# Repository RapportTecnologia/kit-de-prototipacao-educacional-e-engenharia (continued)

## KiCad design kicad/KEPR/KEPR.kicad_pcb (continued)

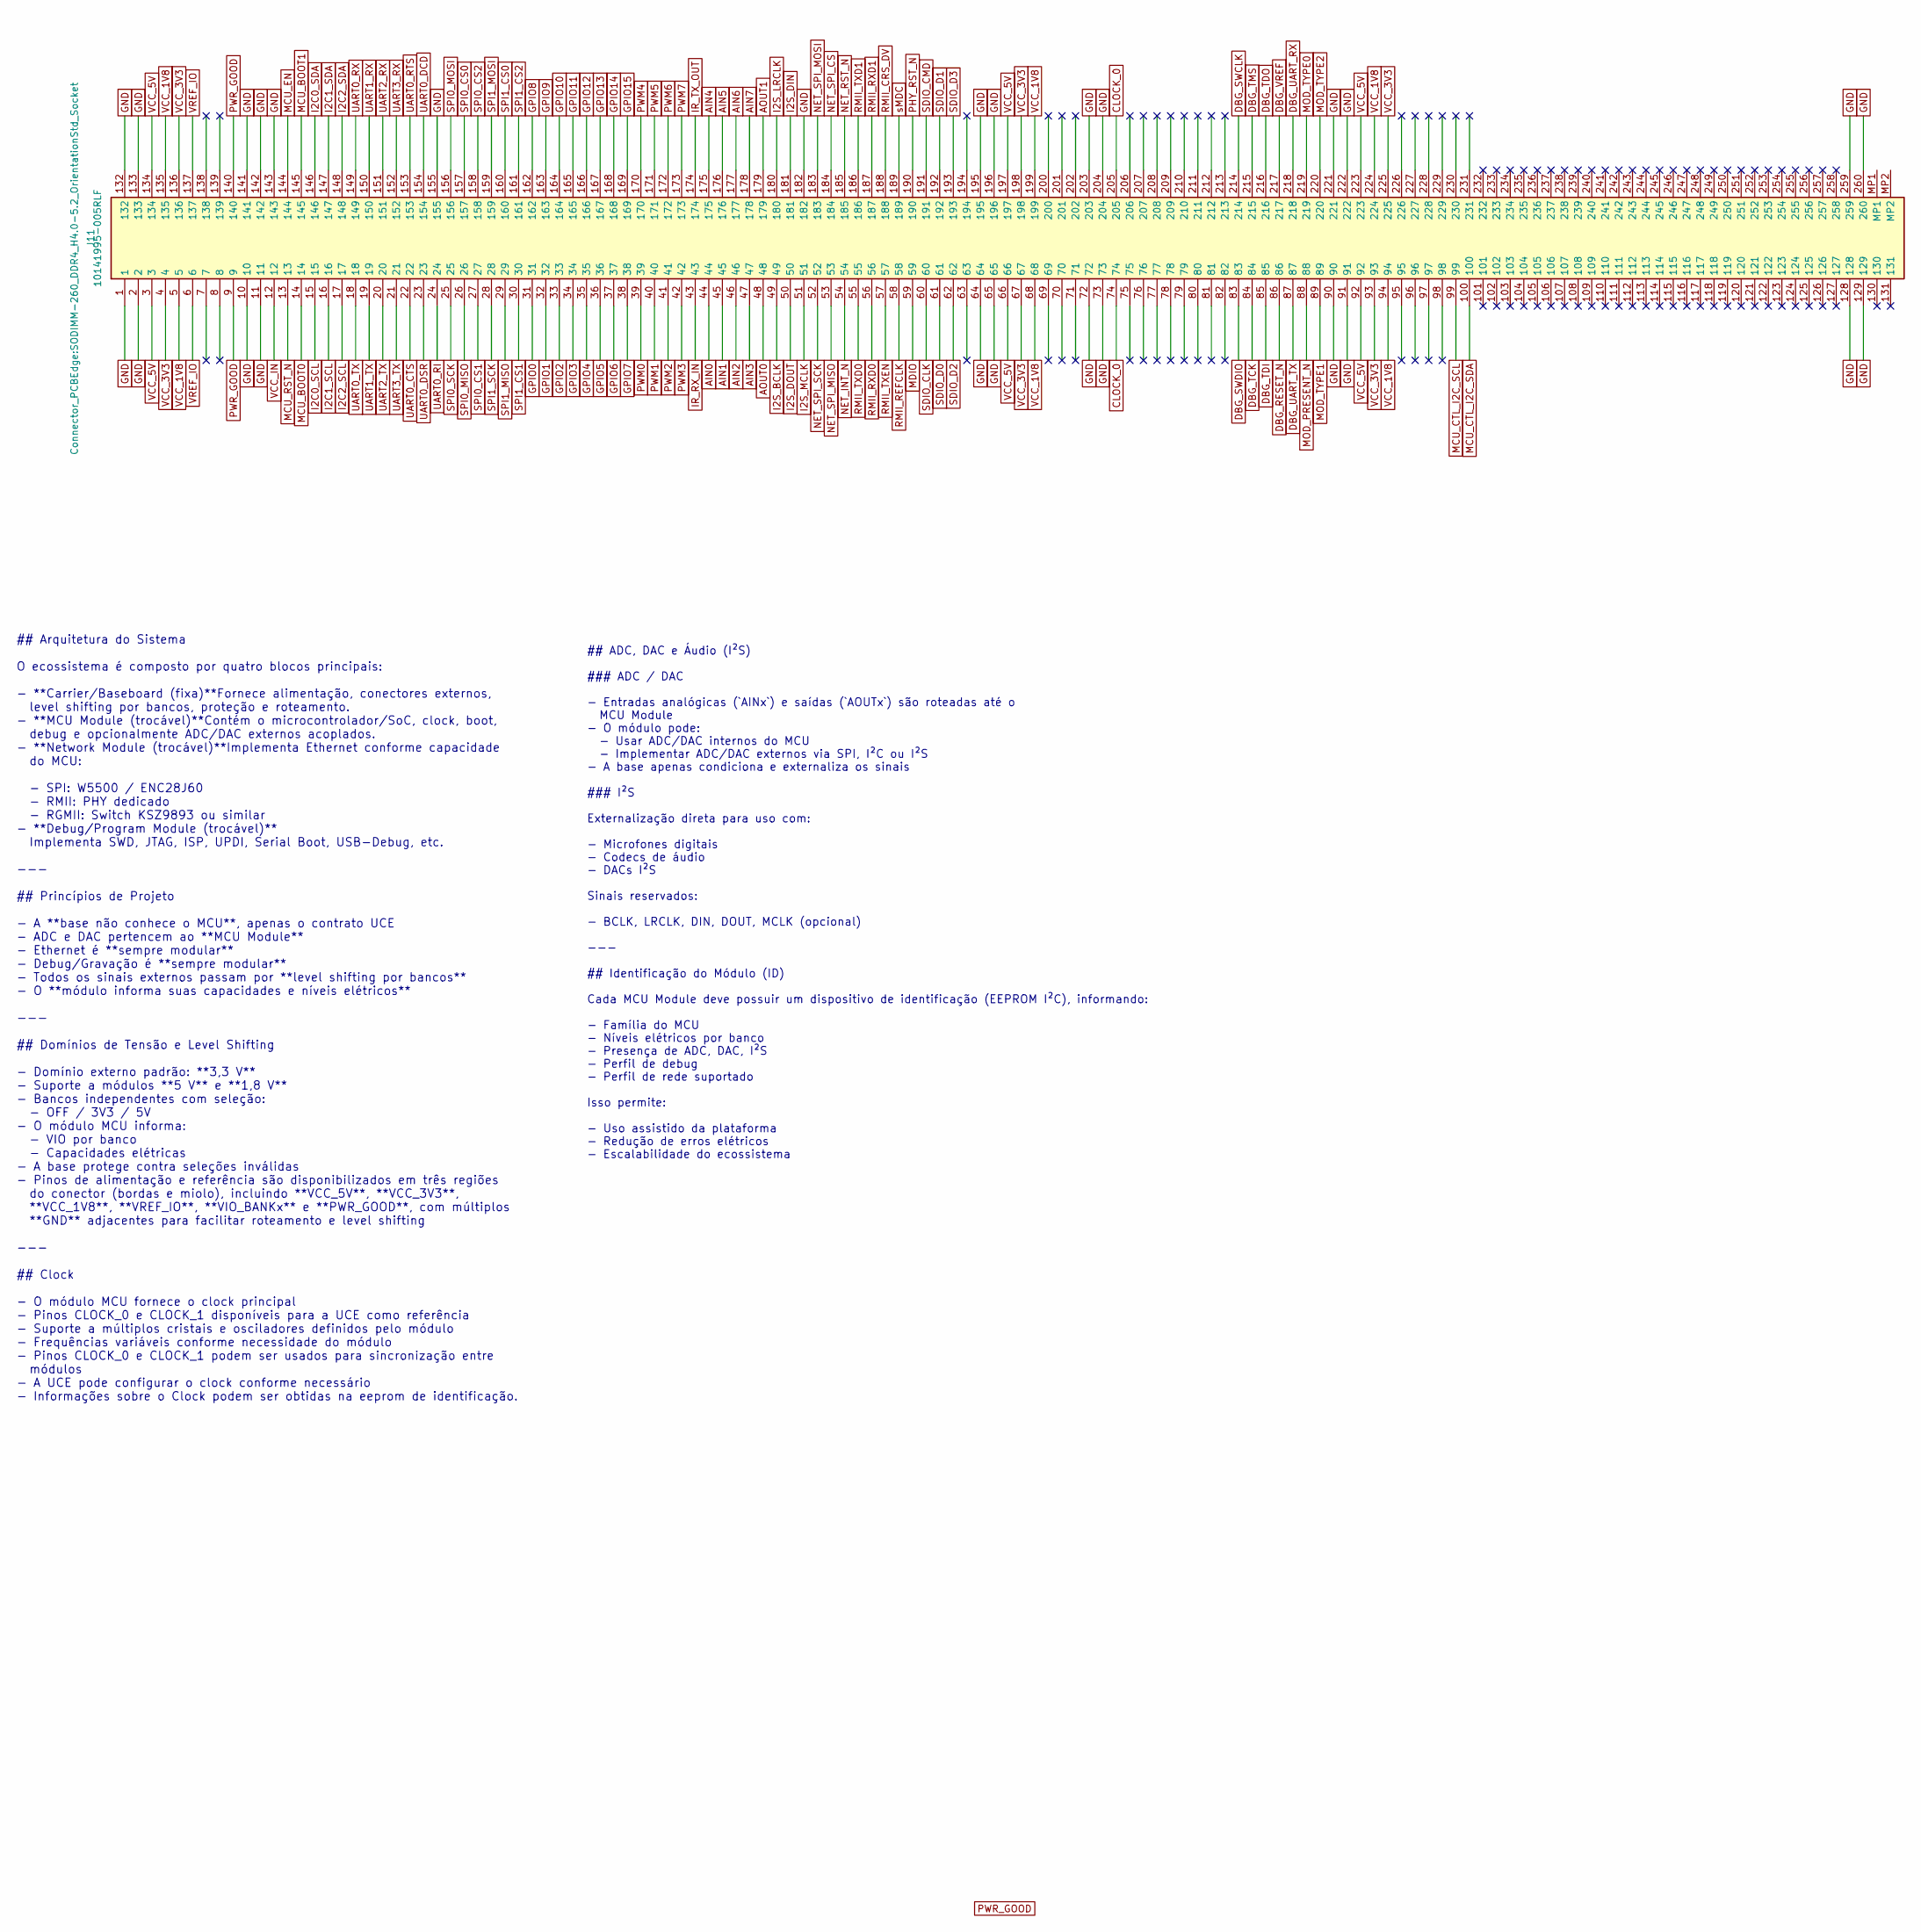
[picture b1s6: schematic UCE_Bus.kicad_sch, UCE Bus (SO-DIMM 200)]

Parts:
J11: 10141995-005RLF; SODIMM-260_DDR4_H4.0-5.2_OrientationStd_Socket; Manufacturer_Part_Number 10141995-005RLF

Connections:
+1v8: J11.5, J11.68, J11.94, J11.135, J11.199, J11.224; also elsewhere on the board
+3.3V: J11.4, J11.67, J11.93, J11.136, J11.198, J11.225; also elsewhere on the board
+5V: J11.3, J11.66, J11.92, J11.134, J11.197, J11.223; also elsewhere on the board
AIN0: J11.44; also elsewhere on the board
AIN1: J11.45; also elsewhere on the board
AIN2: J11.46; also elsewhere on the board
AIN3: J11.47; also elsewhere on the board
AIN4: J11.175; also elsewhere on the board
AIN5: J11.176; also elsewhere on the board
AIN6: J11.177; also elsewhere on the board
AIN7: J11.178; also elsewhere on the board
AOUT0: J11.48; also elsewhere on the board
AOUT1: J11.179; also elsewhere on the board
CLOCK_0: J11.74, J11.205; also elsewhere on the board
DBG_RESET_N: J11.86; also elsewhere on the board
DBG_SWCLK: J11.214; also elsewhere on the board
DBG_SWDIO: J11.83; also elsewhere on the board
DBG_TCK: J11.84; also elsewhere on the board
DBG_TDI: J11.85; also elsewhere on the board
DBG_TDO: J11.216; also elsewhere on the board
DBG_TMS: J11.215; also elsewhere on the board
DBG_UART_RX: J11.218; also elsewhere on the board
DBG_UART_TX: J11.87; also elsewhere on the board
DBG_VREF: J11.217; also elsewhere on the board
GND: J11.1, J11.2, J11.10, J11.11, J11.64, J11.65, J11.72, J11.73, J11.90, J11.91, J11.128, J11.129, J11.132, J11.133, J11.141, J11.142, J11.143, J11.155, J11.182, J11.195, J11.196, J11.203, J11.204, J11.221, J11.222, J11.259, J11.260; also elsewhere on the board
GPIO0: J11.31; also elsewhere on the board
GPIO1: J11.32; also elsewhere on the board
GPIO2: J11.33; also elsewhere on the board
GPIO3: J11.34; also elsewhere on the board
GPIO4: J11.35; also elsewhere on the board
GPIO5: J11.36; also elsewhere on the board
GPIO6: J11.37; also elsewhere on the board
GPIO7: J11.38; also elsewhere on the board
GPIO8: J11.162; also elsewhere on the board
GPIO9: J11.163; also elsewhere on the board
GPIO10: J11.164; also elsewhere on the board
GPIO11: J11.165; also elsewhere on the board
GPIO12: J11.166; also elsewhere on the board
GPIO13: J11.167; also elsewhere on the board
GPIO14: J11.168; also elsewhere on the board
GPIO15: J11.169; also elsewhere on the board
I2C0_SCL: J11.15; also elsewhere on the board
I2C0_SDA: J11.146; also elsewhere on the board
I2C1_SCL: J11.16; also elsewhere on the board
I2C1_SDA: J11.147; also elsewhere on the board
I2C2_SCL: J11.17; also elsewhere on the board
I2C2_SDA: J11.148; also elsewhere on the board
I2S_BCLK: J11.49; also elsewhere on the board
I2S_DIN: J11.181; also elsewhere on the board
I2S_DOUT: J11.50; also elsewhere on the board
I2S_LRCLK: J11.180; also elsewhere on the board
I2S_MCLK: J11.51; also elsewhere on the board
IR_RX_IN: J11.43; also elsewhere on the board
IR_TX_OUT: J11.174; also elsewhere on the board
MCU_BOOT0: J11.14; also elsewhere on the board
MCU_BOOT1: J11.145; also elsewhere on the board
MCU_CTL_I2C_SCL: J11.99; also elsewhere on the board
MCU_CTL_I2C_SDA: J11.100; also elsewhere on the board
MCU_EN: J11.144; also elsewhere on the board
MCU_RST_N: J11.13; also elsewhere on the board
MDIO: J11.59; also elsewhere on the board
MOD_PRESENT_N: J11.88; also elsewhere on the board
MOD_TYPE0: J11.219; also elsewhere on the board
MOD_TYPE1: J11.89; also elsewhere on the board
MOD_TYPE2: J11.220; also elsewhere on the board
NET_CLK_ODD: J11.58; also elsewhere on the board
NET_CTL0_EVEN: J11.184; also elsewhere on the board
NET_CTL0_ODD: J11.57; also elsewhere on the board
NET_CTL1_ODD: J11.188; also elsewhere on the board
NET_CTL2_ODD: J11.189, J11.190; also elsewhere on the board
NET_D0_EVEN: J11.183; also elsewhere on the board
NET_D2_EVEN: J11.53; also elsewhere on the board
NET_INT_N: J11.54
NET_RST_N: J11.185
NET_SPI_SCK: J11.52
PWM0: J11.39; also elsewhere on the board
PWM1: J11.40; also elsewhere on the board
PWM2: J11.41; also elsewhere on the board
PWM3: J11.42; also elsewhere on the board
PWM4: J11.170; also elsewhere on the board
PWM5: J11.171; also elsewhere on the board
PWM6: J11.172; also elsewhere on the board
PWM7: J11.173; also elsewhere on the board
PWR_GOOD: J11.9, J11.140; also elsewhere on the board
RMII_RXD0: J11.56
RMII_RXD1: J11.187
RMII_TXD0: J11.55
RMII_TXD1: J11.186
SDIO_CLK: J11.60, J11.61; also elsewhere on the board
SDIO_CMD: J11.191; also elsewhere on the board
SDIO_D1: J11.192; also elsewhere on the board
SDIO_D2: J11.62; also elsewhere on the board
SDIO_D3: J11.193; also elsewhere on the board
SPI0_CS0: J11.157; also elsewhere on the board
SPI0_CS1: J11.27; also elsewhere on the board
SPI0_CS2: J11.158; also elsewhere on the board
SPI0_MISO: J11.26; also elsewhere on the board
SPI0_MOSI: J11.156; also elsewhere on the board
SPI0_SCK: J11.25; also elsewhere on the board
SPI1_CS0: J11.160; also elsewhere on the board
SPI1_CS1: J11.30; also elsewhere on the board
SPI1_CS2: J11.161; also elsewhere on the board
SPI1_MISO: J11.29; also elsewhere on the board
SPI1_MOSI: J11.159; also elsewhere on the board
SPI1_SCK: J11.28; also elsewhere on the board
UART0_CTS: J11.22; also elsewhere on the board
UART0_DCD: J11.154; also elsewhere on the board
UART0_DSR: J11.23; also elsewhere on the board
UART0_RI: J11.24; also elsewhere on the board
UART0_RTS: J11.153; also elsewhere on the board
UART0_RX: J11.149; also elsewhere on the board
UART0_TX: J11.18; also elsewhere on the board
UART1_RX: J11.150; also elsewhere on the board
UART1_TX: J11.19; also elsewhere on the board
UART2_RX: J11.151; also elsewhere on the board
UART2_TX: J11.20; also elsewhere on the board
UART3_RX: J11.152; also elsewhere on the board
UART3_TX: J11.21; also elsewhere on the board
VCC_IN: J11.12; also elsewhere on the board
VREF_IO: J11.6, J11.137; also elsewhere on the board

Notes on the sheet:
## Arquitetura do Sistema O ecossistema é composto por quatro blocos principais: - **Carrier/Baseboard (fixa)**Fornece alimentação, conectores externos, level shifting por bancos, proteção e roteamento. - **MCU Module (trocável)**Contém o microcontrolador/SoC, clock, boot, debug e opcionalmente ADC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
## ADC, DAC e Áudio (I²S) ### ADC / DAC - Entradas analógicas (`AINx`) e saídas (`AOUTx`) são roteadas até o MCU Module - O módulo pode: - Usar ADC/DAC internos do MCU - Implementar ADC/DAC externos via SPI, I²C ou I²S - A base apenas condiciona e externaliza os sinais ### I²S Externalização direta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

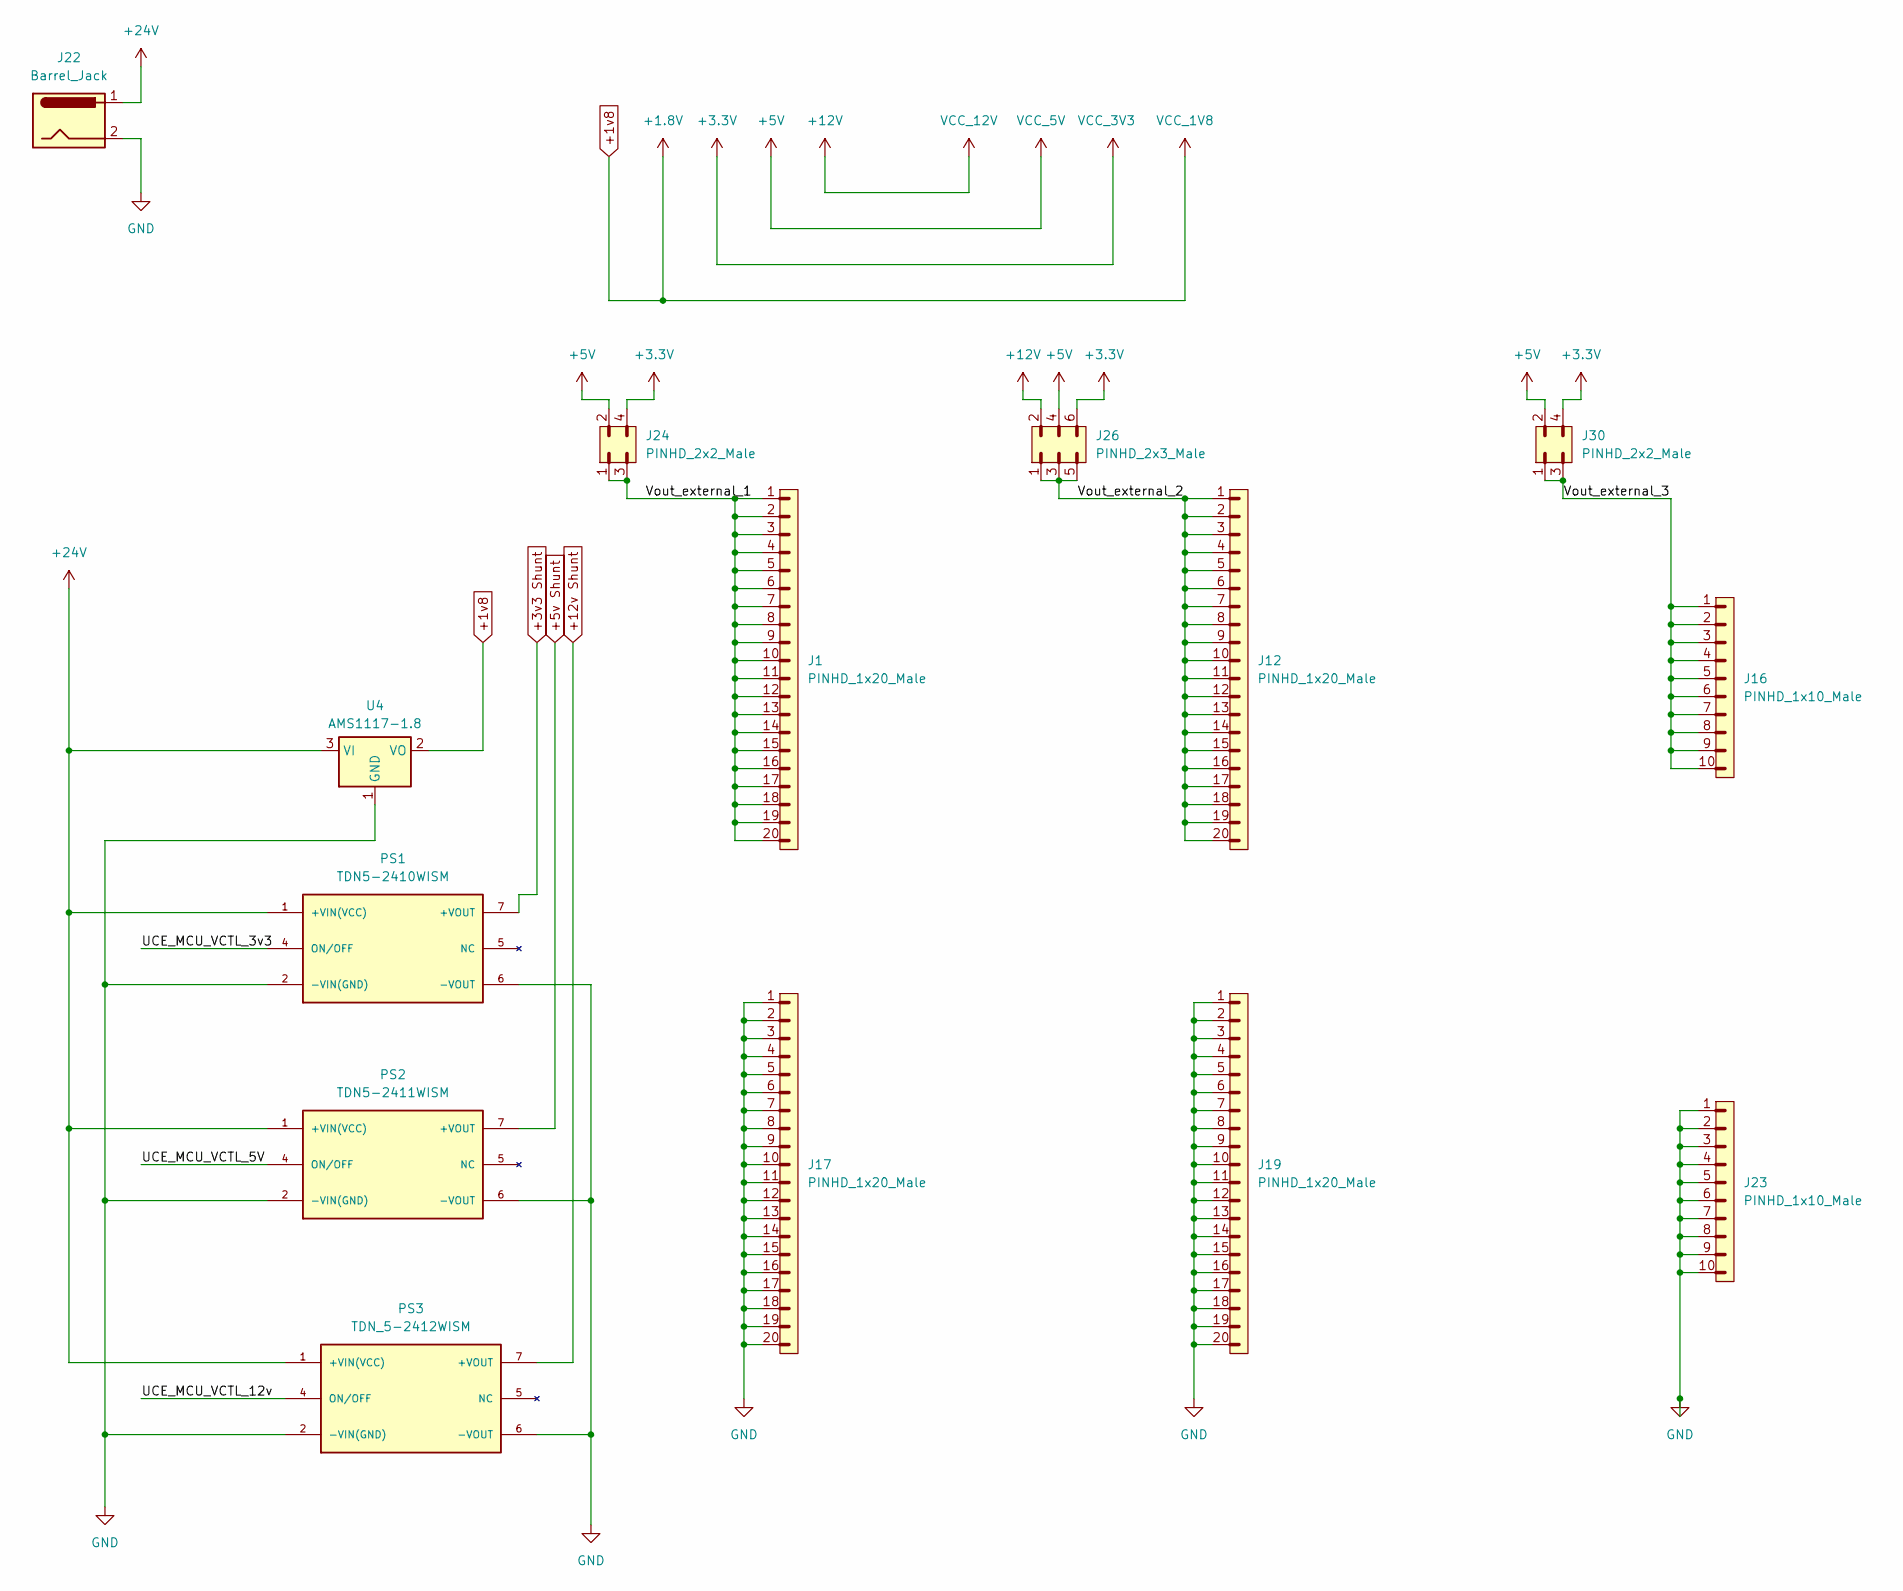
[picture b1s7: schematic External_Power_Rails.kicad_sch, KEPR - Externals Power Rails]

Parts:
J1, J12, J17, J19: PINHD_1x20_Male; PinHeader_1x20_P2.54mm_Vertical
J16, J23: PINHD_1x10_Male; PinHeader_1x10_P2.54mm_Vertical
J22: Barrel_Jack; BarrelJack_Horizontal
J24, J30: PINHD_2x2_Male; PinHeader_2x02_P2.54mm_Vertical
J26: PINHD_2x3_Male; PinHeader_2x03_P2.54mm_Vertical
PS1: TDN5-2410WISM; CONV_TDN5-2411WISM; PARTREV May 18, 2020
PS2: TDN5-2411WISM; CONV_TDN5-2411WISM; PARTREV August 17, 2020
PS3: TDN_5-2412WISM; CONV_TDN5-2411WISM; PARTREV August 17, 2020
U4: AMS1117-1.8; SOT-223-3_TabPin2

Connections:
+1v8: U4.2 (VO); also elsewhere on the board
+3.3V: J24.4, J26.6, J30.4; also elsewhere on the board
+3v3 Shunt: PS1.7 (+VOUT); also elsewhere on the board
+5V: J24.2, J26.4, J30.2; also elsewhere on the board
+5v Shunt: PS2.7 (+VOUT); also elsewhere on the board
+12V: J26.2; also elsewhere on the board
+12v Shunt: PS3.7 (+VOUT); also elsewhere on the board
+24V: J22.1, PS1.1 (+VIN(VCC)), PS2.1 (+VIN(VCC)), PS3.1 (+VIN(VCC)), U4.3 (VI)
/Power/Power Rails/UCE_MCU_VCTL_3v3: PS1.4 (ON/OFF)
/Power/Power Rails/UCE_MCU_VCTL_5V: PS2.4 (ON/OFF)
/Power/Power Rails/UCE_MCU_VCTL_12v: PS3.4 (ON/OFF)
/Power/Power Rails/Vout_external_1: J1.1, J1.2, J1.3, J1.4, J1.5, J1.6, J1.7, J1.8, J1.9, J1.10, J1.11, J1.12, J1.13, J1.14, J1.15, J1.16, J1.17, J1.18, J1.19, J1.20, J24.1, J24.3
/Power/Power Rails/Vout_external_2: J12.1, J12.2, J12.3, J12.4, J12.5, J12.6, J12.7, J12.8, J12.9, J12.10, J12.11, J12.12, J12.13, J12.14, J12.15, J12.16, J12.17, J12.18, J12.19, J12.20, J26.1, J26.3, J26.5
/Power/Power Rails/Vout_external_3: J16.1, J16.2, J16.3, J16.4, J16.5, J16.6, J16.7, J16.8, J16.9, J16.10, J30.1, J30.3
GND: J17.1, J17.2, J17.3, J17.4, J17.5, J17.6, J17.7, J17.8, J17.9, J17.10, J17.11, J17.12, J17.13, J17.14, J17.15, J17.16, J17.17, J17.18, J17.19, J17.20, J19.1, J19.2, J19.3, J19.4, J19.5, J19.6, J19.7, J19.8, J19.9, J19.10, J19.11, J19.12, J19.13, J19.14, J19.15, J19.16, J19.17, J19.18, J19.19, J19.20, J22.2, J23.1, J23.2, J23.3, J23.4, J23.5, J23.6, J23.7, J23.8, J23.9, J23.10, PS1.2 (-VIN(GND)), PS1.6 (-VOUT), PS2.2 (-VIN(GND)), PS2.6 (-VOUT), PS3.2 (-VIN(GND)), PS3.6 (-VOUT), U4.1 (GND); also elsewhere on the board

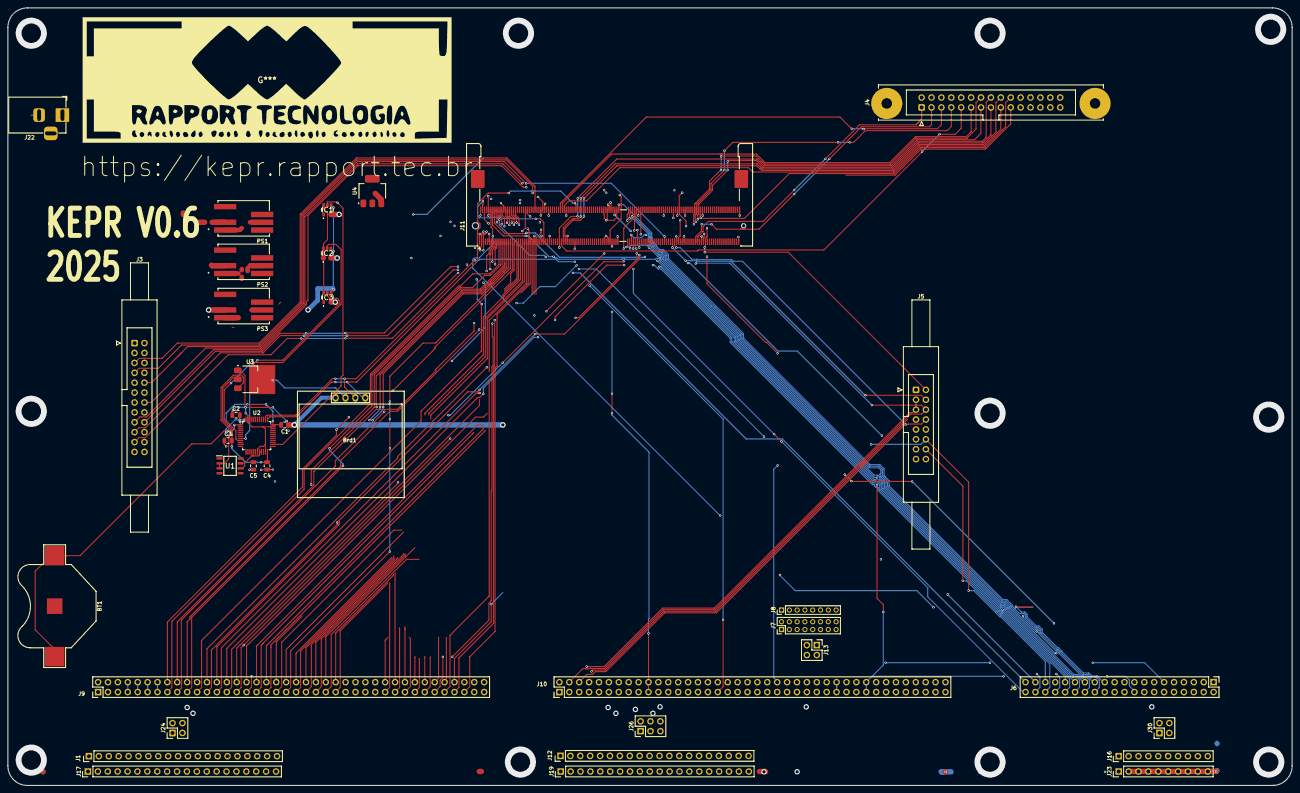
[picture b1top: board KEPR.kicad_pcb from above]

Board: 4 copper layers, 329.5 x 199.5 mm, 37 parts (0 on the bottom side), 128 nets.

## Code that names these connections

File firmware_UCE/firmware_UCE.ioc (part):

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Mcu.Name=STM32G484CETx
Mcu.Package=LQFP48
Mcu.UserName=STM32G484CETx
PA0.Mode=IN1-Single-Ended
PA0.Signal=ADC1_IN1
PA1.Mode=IN2-Single-Ended
PA1.Signal=ADC2_IN2
PA13.Mode=I2C
PA13.Signal=I2C1_SCL
PA14.Mode=I2C
PA14.Signal=I2C1_SDA
PB12.Mode=IN3-Single-Ended
PB12.Signal=ADC4_IN3
RCC.HSE_VALUE=8000000
RCC.SYSCLKFreq_VALUE=16000000
board=custom

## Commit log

2025-12-31 Inicio vercionamento do projeto no release 0.4
2025-12-31 Primeiros documentos.
2025-12-31 Projeto KiCAD
2025-12-31 Adicionado Clock e ajuste na ordenação númerica
2025-12-31 Finalizado versão 0.4 do conector do UCE para o módulo.
2025-12-31 Correção no pino reservado que é mais adequado como GND
2025-12-31 Ajustado a hierarquia de esquemáticos para melhorar o planejamento da placa.
2025-12-31 Versão 0.5 sendo trabalhada.
2026-01-01 Definido os demais buses, criado folha do carimbo, versão 0.5
2026-01-01 Adicinado o barramento externo
2026-01-01 Iniciado projeto da PCB, para uma referência de tamanho.
2026-01-01 Create CNAME
2026-01-01 Update CNAME
2026-01-01 Adicionado Footprints, criado a visualização da PCB
2026-01-01 Melhorias no texto e adicionado a licença do projeto.
2026-01-01 Criado um Website para o projeto.
2026-01-01 geração automática da imagem e exibição no site.
2026-01-01 ci: update KEPR PCB images
2026-01-02 Remove cron schedule from kicad-ci workflow
    Removed scheduled cron job from workflow dispatch.
2026-01-07 ajustado as folhas de desenho para padronizar o nome.
2026-01-07 Removido as folhas antigas.
2026-01-07 Ajuste das estampas conforme NBR
2026-01-07 Vários ajuste, sendo o mais importante a adição do power rail e iniciado o Wireless module
2026-01-07 Mais arquivos a serem ignorados.
2026-01-07 mais ajustes no power rail inclusive com imagem 3d
2026-01-07 Mais ajustes nas folhas de esquemático no Power Rails
2026-01-08 Ajustado na geração da vista 3d da placa
2026-01-08 Adicionado conversores DC-DC e Logo da Rapport
2026-01-08 Datasheet e appnotes para MCUs
2026-01-08 Ativado LFS para lidar com PDFs grandes
2026-01-08 Ajuste no layout do site, ainda precisa melhorar muito.
2026-01-08 Datasheets, Appnotes
2026-01-08 Appnote sobre gerenciamento de energia
2026-01-08 Ignorando arquivos desnecessários no repositório.
2026-01-08 Adcicionado lista de fornecedores, e menu para acesso
2026-01-08 Application note sobre implementação de sistemas de gerenciamento de energia
2026-01-08 Application note para stm32h74xig and stm3275xig family
2026-01-08 Datasheet para Shunts
2026-01-08 Datasheets Resistores
2026-01-08 Mais informações sobre microcontroladores
2026-01-08 Mais um datasheet para estudo de um mcu para controle da UCE
    Estou pesquisando qual o melhor microcontrolador para fazer o controle
    da placa mãe UCE, tenho tido problemas quanto ao uso dos opamps,
    acredito que terei que usar externamente.
2026-01-08 Diversos ajustes no Power Rail
2026-01-08 Adicionado Google Analytics
2026-01-08 Mais ajustes no roteamento
2026-01-08 Iniciado o projeto do Firmware do UCE
2026-01-09 Removido a inclinação da placa, pois não está aceitando a chave de comando
2026-01-09 Agora cria top e botton
2026-01-09 Guias e Manuais da Sierra Circuits
2026-01-09 Datasheet sobre Sensores de Corrente
2026-01-09 Como calcular a corrente no Power Rail e identificar a tensão efetiva
2026-01-09 Ajustes para uso do FreeRTOS e parametros dos ADCs
2026-01-09 Tutorial sobre calculo do Zener para regular tensão do STM32G484CETx
2026-01-09 Mais datasheet
2026-01-09 Datasheet sobre mosFET adequado para sheeftregister
2026-01-09 Melhorado o README, adicionado contador de visitas e licença
2026-01-09 Automátizado a geração de lista BOM e esquemáticos.
2026-01-09 Ajuste na página de exibição da pcb
2026-01-09 Ajuste na geração da imagem 2D
2026-01-09 Adicionado o menu esquemático
2026-01-09 Postagens como tutoriais e informações do projeto
2026-01-09 Diversos ajustes como páginas par acategorias, mais páginas de informação
2026-01-09 Infomrações sobre Alimentação do Kepr
2026-01-09 Tutorial sobre soluções de proteção de tensões reversas e sobretenção
2026-01-09 Melhorias na exibição de esquemáticos
2026-01-09 Ajuste nos relatórios de ERC e DRC
2026-01-09 imagens removidas para serem regeradas no CI
2026-01-09 Ajuste no tamanho do menu Recursos
2026-01-09 Ajuste na listagem de artigos.
2026-01-09 Ajuste na exibição dos relatórios ERC-DRC
2026-01-09 Gera os esquemáticos para uso nas páginas do site
2026-01-09 Gera o relatório ERC e DRC para exibir no site
2026-01-09 Tutoriais e Guias da Sierra Circuits
2026-01-09 Livro do KiCAD
2026-01-09 Script e CI para gerar a lista de livros
2026-01-09 eBook que ensina sobre pares diferenciais
2026-01-09 Guias da Essentra
2026-01-09 eBook Duplicado
2026-01-09 mais eBooks
2026-01-09 Normas
2026-01-09 Tutorial e guia da Analog Devices
2026-01-09 Mais datasheets e app notes, ignorado os que são irrelevantes atualmente
2026-01-09 Ajustes no Power Rail, entre outros ajustes.
2026-01-09 Adicionado holder para bateria.
2026-01-09 Corrigido erros na sintaxe e lógica
2026-01-09 Mais appnote sobre Current Sensors
2026-01-09 Correção do permalink
2026-01-09 Correção da disponibilidde das imagens.
2026-01-09 Correção na geração de lista de datasheets
2026-01-09 Corrigido Formatação
2026-01-09 Correção na exibição das capas
2026-01-10 Artigo sobre o mercado de microcontroladores
2026-01-10 Nova fonte de bibliotecas para o kicad
2026-01-10 Adicionado mais uma fonte de footprints
2026-01-10 Datasheet sobre reguladores de tensão.
2026-01-10 Desativdo no firmware o uso dos OpAmps e reconfiugaração dos ADCs
2026-01-10 Troca dos sensores de corrente e conversores de tensão para o MCU controlador
2026-01-10 Adicionado um novo fornecedor de bibliotecas.
2026-01-10 Atualizado informações para a versão 0.6
2026-01-10 Datasheet sobre ams1117
2026-01-10 Ajustado links para que sejam clicáveis, ajustado o nome da página Fornecedores
2026-01-11 Iniciado a distribuição das vias.
2026-01-11 Ignorando o diretório do vscode.
2026-01-11 Mais datasheets, datasheet de regulares de tensão.
2026-01-11 Teclas de atalho do KiCAD
2026-01-11 Correção no nome do Autor para diferenciar do outro eBook
2026-01-11 Adicionado a primeira versão da MCU Board, inicado com STM32N6
2026-01-12 Novo datasheet com medidas do conector Sodimm DDR4 260pinos
2026-01-12 Layout da placa para encaixe no SODIMM 260pin
2026-01-12 Ajustes para o MCU Board STM32N6
2026-01-12 ainda fazendo testes de composição das placas.
2026-01-12 Verificando a compatibilidade do geber com o corte multiplaca
2026-01-12 ainda fazendo testes com o Gerbers
2026-01-12 Ignorando arquivos zip, pois são produtos temporários.
2026-01-12 Script para gerar multiplas placas(pcb) e multiplos BOM
2026-01-12 Guia sobre IPC 2152
2026-01-12 Mais eBook
2026-01-12 Diversos ajustes no barramento e ampliação das trilhas na PCB
2026-01-12 Correção do nome do arquivo
2026-01-13 Adicionado o display oled e mais trilhas.
2026-01-13 Removido pcb do módulo sodimm de referência.
2026-01-13 Corrigido novamente a url dos relatórios
2026-01-14 Ajustando trilhas
2026-01-15 mais ajustes de trilha.
2026-01-15 Mais eBooks e organizando alguns arquivos.
2026-01-16 Mais trilhas e vias lançadas
2026-02-05 Correção dos nomes.
